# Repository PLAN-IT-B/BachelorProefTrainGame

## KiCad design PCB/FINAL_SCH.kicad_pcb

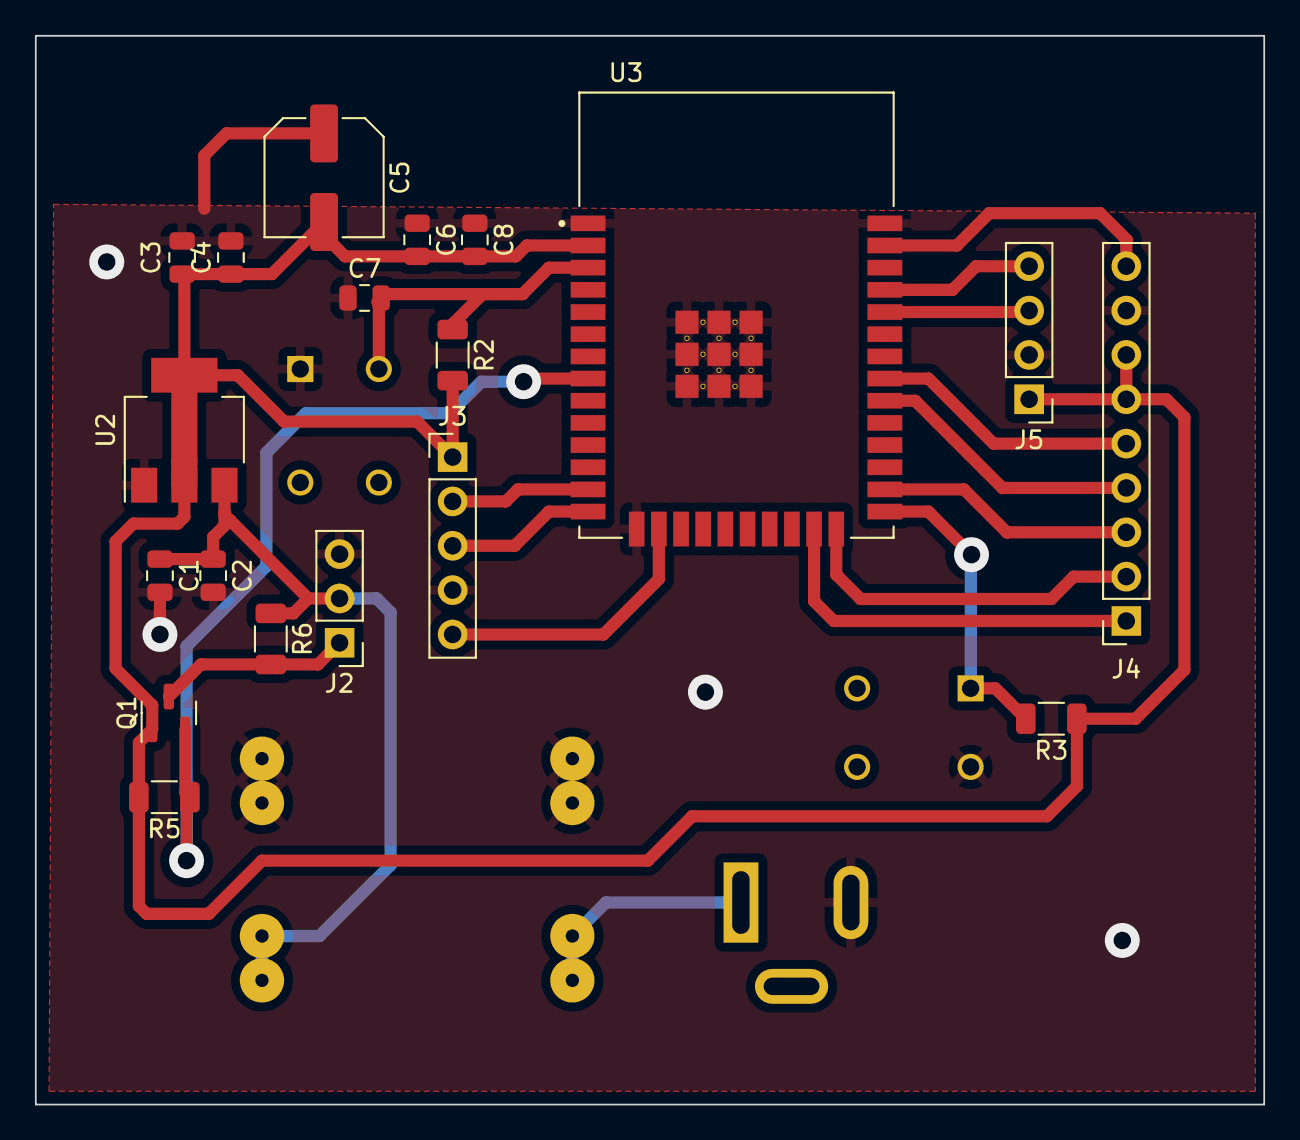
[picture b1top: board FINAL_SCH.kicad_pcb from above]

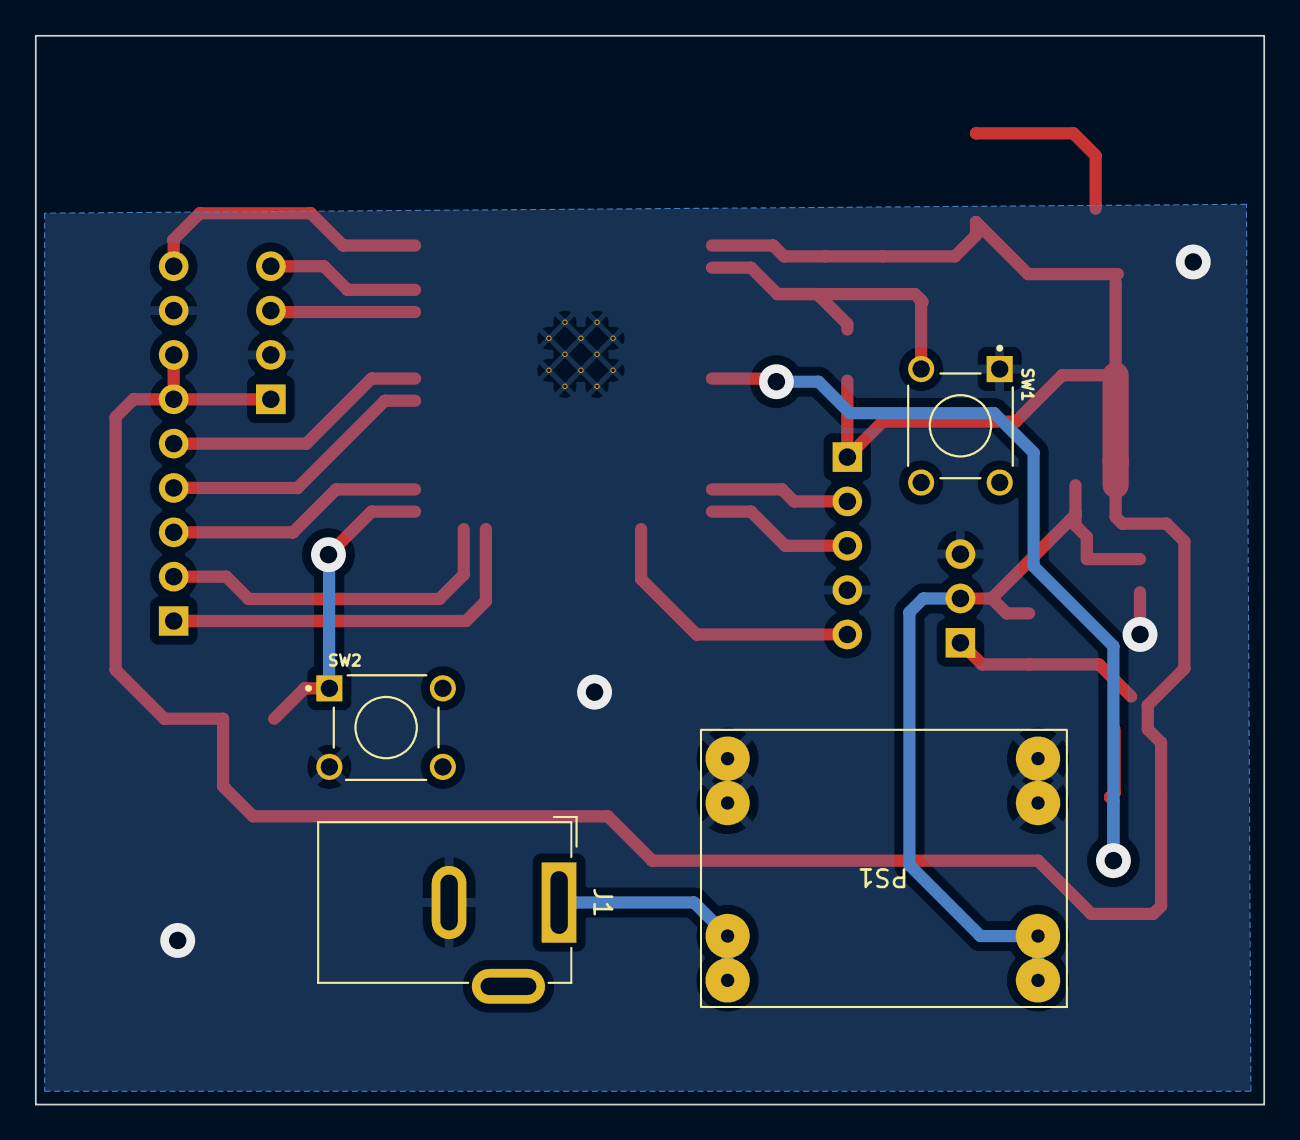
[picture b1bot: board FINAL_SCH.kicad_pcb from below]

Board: 2 copper layers, 70.4 x 61.2 mm, 23 parts (4 on the bottom side), 19 nets.

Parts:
C1, C4: 4.7u; C_0805_2012Metric
C2, C3, C8: 0.1u; C_0805_2012Metric
C5: 220u; C_Elec_6.3x7.7
C6: 22u; C_0805_2012Metric
C7: 1uF; C_0805_2012Metric
J1: Barrel_Jack; BarrelJack_GCT_DCJ200-10-A_Horizontal
J2: Conn_01x03_Male; PinHeader_1x03_P2.54mm_Vertical
J3: Conn_01x05_Male; PinHeader_1x05_P2.54mm_Vertical
J4: Conn_01x09_Male; PinSocket_1x09_P2.54mm_Vertical
J5: Conn_01x04_Male; PinHeader_1x04_P2.54mm_Vertical
PS1: ITX0512SA; Buck_Converter
Q1: BSS138; SOT-23
R2, R3, R5, R6: 10k; R_1206_3216Metric
SW1, SW2: SW_Push; SW_1825910-6-4
U2: AMS1117; SOT-223-3_TabPin2
U3: ESP32-WROOM-32D; MODULE_ESP32-WROOM-32D

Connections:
3V3: C3.1, C4.1, C5.2, C6.2, C8.2, J3.1, J4.6, J4.7, J5.1, Q1.1 (G), R2.2, R3.1, R5.2, U2.2 (VO), U3.2 (3V3)
5V: C1.1, C2.1, J2.2, PS1.3a (+Vout), PS1.3b (+Vout), R6.1, U2.3 (VI)
12V: J1.1, PS1.1a (+Vin), PS1.1b (+Vin)
GND: C1.2, C2.2, C3.2, C4.2, C5.1, C6.1, C7.1, C8.1, J1.2, J2.3, J3.4, J4.8, J5.2, PS1.2a (-Vin), PS1.2b (-Vin), PS1.4a (-Vout), PS1.4b (-Vout), SW1.1, SW2.2, U2.1 (ADJ), U3.1 (GND), U3.15 (GND), U3.38 (GND), U3.39_1 (GND), U3.39_2 (GND), U3.39_3 (GND), U3.39_4 (GND), U3.39_5 (GND), U3.39_6 (GND), U3.39_7 (GND), U3.39_8 (GND), U3.39_9 (GND), U3.39_10 (GND), U3.39_11 (GND), U3.39_12 (GND), U3.39_13 (GND), U3.39_14 (GND), U3.39_15 (GND), U3.39_16 (GND), U3.39_17 (GND), U3.39_18 (GND), U3.39_19 (GND), U3.39_20 (GND), U3.39_21 (GND)
JS_SW: J3.5, U3.16 (IO13)
JS_X: J3.3, U3.14 (IO12)
JS_Y: J3.2, U3.13 (IO14)
LCD_CS: J4.1, U3.23 (IO15)
LCD_DC: J4.2, U3.24 (IO2)
LCD_RST: J4.3, U3.26 (IO4)
LCD_SCK: J4.4, U3.30 (IO18)
LCD_SDIMOSI: J4.9, U3.37 (IO23)
LCD_SDOMISO: J4.5, U3.31 (IO19)
LED_DATA: J2.1, Q1.3 (D), R6.2
unnamed: C7.2, R2.1, SW1.2, U3.3 (EN)
unnamed: Q1.2 (S), R5.1, U3.8 (IO32)
unnamed: R3.2, SW2.1, U3.25 (IO0)
RX: J5.3, U3.34 (RXD0)
TX: J5.4, U3.35 (TXD0)

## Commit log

2022-02-22 Setup
2022-02-22 Verplaatsing Drukknop.h
2022-02-22 Verfijning Drukknop.h
2022-02-22 Create timeline - Escape Room.xlsx
    gantt-chart
2022-02-22 Add blokschema
2022-03-01 Change Drukknop
2022-03-08 faal
    bogus code
2022-03-17 Update workspace.code-workspace
2022-05-05 Test Your buddy
    file
2022-05-20 STL-files puzzel
2022-05-20 Extra modellen
2022-05-21 Opruimen en sorteren
2022-05-24 files
